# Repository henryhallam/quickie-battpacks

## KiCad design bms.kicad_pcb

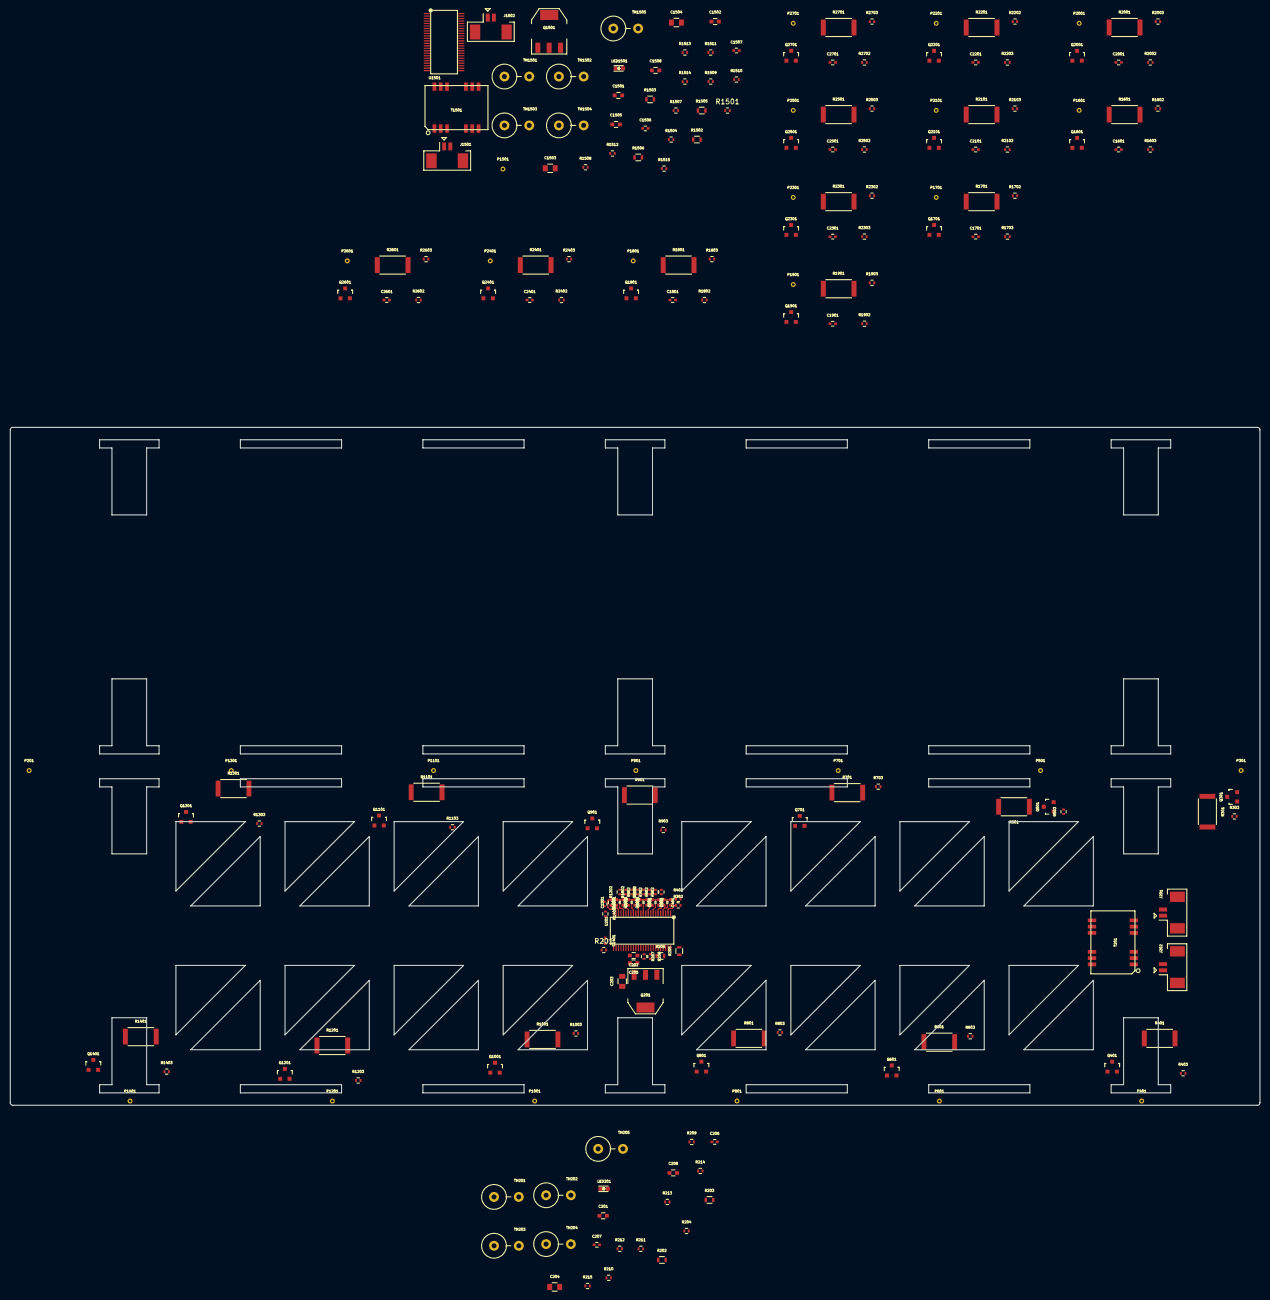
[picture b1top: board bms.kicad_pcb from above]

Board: 2 copper layers, 252.0 x 136.7 mm, 214 parts (0 on the bottom side), 174 nets.

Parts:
C201, C1501: 10nF 16V; C_0603
C202, C205, C208, C1502, C1505, C1508: 1uF 16V; C_0603
C203, C204, C1503, C1504: 0.1uF 100V; C_0805
C206, C207, C1506, C1507: 100pF; C_0402
C301, C401, C501, C601, C701, C801, C901, C1001, C1101, C1201, C1301, C1401, C1601, C1701, C1801, C1901, C2001, C2101, C2201, C2301, C2401, C2501, C2601, C2701: 10nF 16V; C_0402
J201, J202, J1501, J1502: CONN_01X02; Molex_PicoBlade_53261-0271
LED201, LED1501: Led_Small; LED_0603
P201, P301, P401, P501, P601, P701, P801, P901, P1001, P1101, P1201, P1301, P1401, P1501, P1601, P1701, P1801, P1901, P2001, P2101, P2201, P2301, P2401, P2501, P2601, P2701: CONN_01X01; Solder_Point_Round-TH_0.5mm
Q201, Q1501: NSV1C201MZ4; SOT-223
Q301, Q401, Q501, Q601, Q701, Q801, Q901, Q1001, Q1101, Q1201, Q1301, Q1401, Q1601, Q1701, Q1801, Q1901, Q2001, Q2101, Q2201, Q2301, Q2401, Q2501, Q2601, Q2701: DMP3130LQ; SOT-23
R201, R302, R402, R502, R602, R702, R802, R902, R1002, R1102, R1202, R1302, R1402, R1501, R1602, R1702, R1802, R1902, R2002, R2102, R2202, R2302, R2402, R2502, R2602, R2702: 100; R_0402
R202, R203, R1502, R1503: 100; R_0603
R204, R215, R1504, R1515: 1.2k; R_0402
R205, R206, R1505, R1506: 120; R_0603
R207, R208, R210, R211, R212, R213, R214, R1507, R1508, R1510, R1511, R1512, R1513, R1514: 10k; R_0402
R209, R1509: 2.8k; R_0402
R301, R401, R501, R601, R701, R801, R901, R1001, R1101, R1201, R1301, R1401, R1601, R1701, R1801, R1901, R2001, R2101, R2201, R2301, R2401, R2501, R2601, R2701: 10; R_2512
R303, R403, R503, R603, R703, R803, R903, R1003, R1103, R1203, R1303, R1403, R1603, R1703, R1803, R1903, R2003, R2103, R2203, R2303, R2403, R2503, R2603, R2703: 3.3k; R_0402
T201, T1501: HX0068ANL
TH201, TH202, TH203, TH204, TH205, TH1501, TH1502, TH1503, TH1504, TH1505: THERMISTOR; Resistor_Vertical_RM5mm
U201, U1501: LTC6804-1; G-SSOP-48

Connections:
/PackA/C0: C201.2, C1401.2, R201.2, U201.26
/PackA/C1: C1301.2, C1401.1, R1402.1, U201.24
/PackA/C2: C1201.2, C1301.1, R1302.1, U201.22
/PackA/C3: C1101.2, C1201.1, R1202.1, U201.20
/PackA/C4: C1001.2, C1101.1, R1102.1, U201.18
/PackA/C5: C901.2, C1001.1, R1002.1, U201.16
/PackA/C6: C801.2, C901.1, R902.1, U201.14
/PackA/C7: C701.2, C801.1, R802.1, U201.12
/PackA/C8: C601.2, C701.1, R702.1, U201.10
/PackA/C9: C501.2, C601.1, R602.1, U201.8
/PackA/C10: C401.2, C501.1, R502.1, U201.6
/PackA/C11: C301.2, C401.1, R402.1, U201.4
/PackA/C12: C301.1, R302.1, U201.2
/PackA/Cell1/Cell+: P1401.1, Q1401.2, R1301.2, R1402.2
/PackA/Cell2/Cell+: P1301.1, Q1301.2, R1201.2, R1302.2
/PackA/Cell3/Cell+: P1201.1, Q1201.2, R1101.2, R1202.2
/PackA/Cell4/Cell+: P1101.1, Q1101.2, R1001.2, R1102.2
/PackA/Cell5/Cell+: P1001.1, Q1001.2, R901.2, R1002.2
/PackA/Cell6/Cell+: P901.1, Q901.2, R801.2, R902.2
/PackA/Cell7/Cell+: P801.1, Q801.2, R701.2, R802.2
/PackA/Cell8/Cell+: P701.1, Q701.2, R601.2, R702.2
/PackA/Cell9/Cell+: P601.1, Q601.2, R501.2, R602.2
/PackA/Cell10/Cell+: P501.1, Q501.2, R401.2, R502.2
/PackA/Cell11/Cell+: P401.1, Q401.2, R301.2, R402.2
/PackA/DRIVE: Q201.1, U201.38
/PackA/Pack+: P301.1, Q301.2, R202.2, R203.2, R302.2
/PackA/S1: R1403.1, U201.25
/PackA/S2: R1303.1, U201.23
/PackA/S3: R1203.1, U201.21
/PackA/S4: R1103.1, U201.19
/PackA/S5: R1003.1, U201.17
/PackA/S6: R903.1, U201.15
/PackA/S7: R803.1, U201.13
/PackA/S8: R703.1, U201.11
/PackA/S9: R603.1, U201.9
/PackA/S10: R503.1, U201.7
/PackA/S11: R403.1, U201.5
/PackA/S12: R303.1, U201.3
/PackA/TEMP1: R210.1, TH201.1, U201.27
/PackA/TEMP2: R211.1, TH202.1, U201.28
/PackA/TEMP3: R212.1, TH203.1, U201.29
/PackA/TEMP4: R213.1, TH204.1, U201.32
/PackA/TEMP5: LED201.1, R214.1, TH205.1, U201.33
/PackA/V+: C204.1, R202.1, U201.1
/PackA/V-: C201.1, C202.2, C203.2, C204.2, C205.2, C206.2, C207.2, C208.2, P201.1, R201.1, R204.2, R1401.2, TH201.2, TH202.2, TH203.2, TH204.2, TH205.2, U201.30, U201.31
/PackA/VREF1: C202.1, U201.35
/PackA/VREF2: C205.1, R210.2, R211.2, R212.2, R213.2, R214.2, U201.34
/PackA/VREG: C208.1, Q201.3, R207.2, R208.2, R215.2, U201.37
/PackA/isoSPIA+: J202.1, T201.1
/PackA/isoSPIA-: J202.2, T201.2
/PackB/C0: C1501.2, C2701.2, R1501.2, U1501.26
/PackB/C1: C2601.2, C2701.1, R2702.1, U1501.24
/PackB/C2: C2501.2, C2601.1, R2602.1, U1501.22
/PackB/C3: C2401.2, C2501.1, R2502.1, U1501.20
/PackB/C4: C2301.2, C2401.1, R2402.1, U1501.18
/PackB/C5: C2201.2, C2301.1, R2302.1, U1501.16
/PackB/C6: C2101.2, C2201.1, R2202.1, U1501.14
/PackB/C7: C2001.2, C2101.1, R2102.1, U1501.12
/PackB/C8: C1901.2, C2001.1, R2002.1, U1501.10
/PackB/C9: C1801.2, C1901.1, R1902.1, U1501.8
/PackB/C10: C1701.2, C1801.1, R1802.1, U1501.6
/PackB/C11: C1601.2, C1701.1, R1702.1, U1501.4
/PackB/C12: C1601.1, R1602.1, U1501.2
/PackB/Cell1/Cell+: P2701.1, Q2701.2, R2601.2, R2702.2
/PackB/Cell2/Cell+: P2601.1, Q2601.2, R2501.2, R2602.2
/PackB/Cell3/Cell+: P2501.1, Q2501.2, R2401.2, R2502.2
/PackB/Cell4/Cell+: P2401.1, Q2401.2, R2301.2, R2402.2
/PackB/Cell5/Cell+: P2301.1, Q2301.2, R2201.2, R2302.2
/PackB/Cell6/Cell+: P2201.1, Q2201.2, R2101.2, R2202.2
/PackB/Cell7/Cell+: P2101.1, Q2101.2, R2001.2, R2102.2
/PackB/Cell8/Cell+: P2001.1, Q2001.2, R1901.2, R2002.2
/PackB/Cell9/Cell+: P1901.1, Q1901.2, R1801.2, R1902.2
/PackB/Cell10/Cell+: P1801.1, Q1801.2, R1701.2, R1802.2
/PackB/Cell11/Cell+: P1701.1, Q1701.2, R1601.2, R1702.2
/PackB/DRIVE: Q1501.1, U1501.38
/PackB/Pack+: P1601.1, Q1601.2, R1502.2, R1503.2, R1602.2
/PackB/S1: R2703.1, U1501.25
/PackB/S2: R2603.1, U1501.23
/PackB/S3: R2503.1, U1501.21
/PackB/S4: R2403.1, U1501.19
/PackB/S5: R2303.1, U1501.17
/PackB/S6: R2203.1, U1501.15
/PackB/S7: R2103.1, U1501.13
/PackB/S8: R2003.1, U1501.11
/PackB/S9: R1903.1, U1501.9
/PackB/S10: R1803.1, U1501.7
/PackB/S11: R1703.1, U1501.5
/PackB/S12: R1603.1, U1501.3
/PackB/TEMP1: R1510.1, TH1501.1, U1501.27
/PackB/TEMP2: R1511.1, TH1502.1, U1501.28
/PackB/TEMP3: R1512.1, TH1503.1, U1501.29
/PackB/TEMP4: R1513.1, TH1504.1, U1501.32
/PackB/TEMP5: LED1501.1, R1514.1, TH1505.1, U1501.33
/PackB/V+: C1504.1, R1502.1, U1501.1
/PackB/V-: C1501.1, C1502.2, C1503.2, C1504.2, C1505.2, C1506.2, C1507.2, C1508.2, P1501.1, R1501.1, R1504.2, R2701.2, TH1501.2, TH1502.2, TH1503.2, TH1504.2, TH1505.2, U1501.30, U1501.31
/PackB/VREF1: C1502.1, U1501.35
/PackB/VREF2: C1505.1, R1510.2, R1511.2, R1512.2, R1513.2, R1514.2, U1501.34
/PackB/VREG: C1508.1, Q1501.3, R1507.2, R1508.2, R1515.2, U1501.37
/PackB/isoSPIB+: J1501.1, T1501.5
/PackB/isoSPIB-: J1501.2, T1501.6
/isoSPI_P2P_+: J201.1, J1502.1, T201.5, T1501.1
/isoSPI_P2P_-: J201.2, J1502.2, T201.6, T1501.2
unnamed: C203.1, Q201.2, Q201.4, R203.1
unnamed: C206.1, T201.10
unnamed: C207.1, T201.9
unnamed: C1503.1, Q1501.2, Q1501.4, R1503.1
unnamed: C1506.1, T1501.10
unnamed: C1507.1, T1501.9
unnamed: LED201.2, R215.1
unnamed: LED1501.2, R1515.1
unnamed: Q301.1, R303.2
unnamed: Q301.3, R301.1
unnamed: Q401.1, R403.2
unnamed: Q401.3, R401.1
unnamed: Q501.1, R503.2
unnamed: Q501.3, R501.1
unnamed: Q601.1, R603.2
unnamed: Q601.3, R601.1
unnamed: Q701.1, R703.2
unnamed: Q701.3, R701.1
unnamed: Q801.1, R803.2
unnamed: Q801.3, R801.1
unnamed: Q901.1, R903.2
unnamed: Q901.3, R901.1
unnamed: Q1001.1, R1003.2
unnamed: Q1001.3, R1001.1
unnamed: Q1101.1, R1103.2
unnamed: Q1101.3, R1101.1
unnamed: Q1201.1, R1203.2
unnamed: Q1201.3, R1201.1
unnamed: Q1301.1, R1303.2
unnamed: Q1301.3, R1301.1
unnamed: Q1401.1, R1403.2
unnamed: Q1401.3, R1401.1
unnamed: Q1601.1, R1603.2
unnamed: Q1601.3, R1601.1
unnamed: Q1701.1, R1703.2
unnamed: Q1701.3, R1701.1
unnamed: Q1801.1, R1803.2
unnamed: Q1801.3, R1801.1
unnamed: Q1901.1, R1903.2
unnamed: Q1901.3, R1901.1
unnamed: Q2001.1, R2003.2
unnamed: Q2001.3, R2001.1
unnamed: Q2101.1, R2103.2
unnamed: Q2101.3, R2101.1
unnamed: Q2201.1, R2203.2
unnamed: Q2201.3, R2201.1
unnamed: Q2301.1, R2303.2
unnamed: Q2301.3, R2301.1
unnamed: Q2401.1, R2403.2
unnamed: Q2401.3, R2401.1
unnamed: Q2501.1, R2503.2
unnamed: Q2501.3, R2501.1
unnamed: Q2601.1, R2603.2
unnamed: Q2601.3, R2601.1
unnamed: Q2701.1, R2703.2
unnamed: Q2701.3, R2701.1
unnamed: R204.1, R209.2, U201.46
unnamed: R205.1, T201.7, U201.47
unnamed: R205.2, T201.8, U201.48
unnamed: R206.1, T201.11, U201.41
unnamed: R206.2, T201.12, U201.42
unnamed: R207.1, U201.36
unnamed: R208.1, U201.40
unnamed: R209.1, U201.45
unnamed: R1504.1, R1509.2, U1501.46
unnamed: R1505.1, T1501.7, U1501.47
unnamed: R1505.2, T1501.8, U1501.48
unnamed: R1506.1, T1501.11, U1501.41
unnamed: R1506.2, T1501.12, U1501.42
unnamed: R1507.1, U1501.36
unnamed: R1508.1, U1501.40
unnamed: R1509.1, U1501.45

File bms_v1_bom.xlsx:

Reference Designator | Quantity | Description/Value | Manufacturer Part Number (MPN)
REF**,REF**,REF**,REF**,REF**,REF**,REF** | 7 | Fiducials | DNP
C501,C301,C401,C601,C701,C801,C901,C1001,C1101,C1201,C1301,C1401,C201,C1501,C16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 | 26 | CAP CER 0.01uF 50V | GCM155R71H103KA55D
C202,C205,C208,C1502,C1505,C1508 | 6 | CAP CER 1uF 16V | GCM188R71C105KA64D
C203,C204,C1503,C1504 | 4 | CAP CER 0.1uF 250V | CGA4J3X7T2E104M125AE
J201,J202,J1501,J1502 | 4 | Conn Picoblade 2pos | 53261-0271
Q201,Q1501 | 2 | Transistor NPN | NSV1C201MZ4
Q301,Q401,Q501,Q601,Q701,Q801,Q901,Q1001,Q1101,Q1201,Q1301,Q1401,Q1601,Q1701,Q1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 | 24 | MOSFET P-CH 3A | DMP3130LQ
R202,R203,R1502,R1503 | 4 | RES 100R 1% | ERJ-3EKF1000V
R205,R206,R1505,R1506 | 4 | RES 120R 1% | ERJ-3EKF1200V
R301,R401,R501,R601,R701,R801,R901,R1001,R1101,R1201,R1301,R1401,R1601,R1701,R1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 | 24 | RES 10R 5% 3W | 352210RJT
T201,T1501 | 2 | Transformer pulse | HX0068ANL
U201,U1501 | 2 | IC MONITOR BATT STACK | LTC6804HG-1
P201,P301,P401,P501,P601,P701,P801,P901,P1001,P1101,P1201,P1301,P1401,P1501,P16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 | 26 | Solder point | DNP
C206,C207,C1506,C1507 | 4 | CAP CER 100pF 50V | CGJ2B2C0G1H101J050BA
R204,R1504 | 2 | RES 1.2K 1% | ERJ-2RKF1201X
R207,R208,R210,R211,R212,R213,R214,R1507,R1508,R1510,R1511,R1512,R1513,R1514 | 14 | RES 10K 0.1% | ERA-2AEB103X
R302,R402,R502,R602,R702,R802,R902,R1002,R1102,R1202,R1302,R1402,R201,R1501,R16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 | 26 | RES 100R 1% | ERJ-2RKF1000X
R209,R303,R403,R503,R603,R703,R803,R903,R1003,R1103,R1203,R1303,R1403,R1509,R16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 | 24 | RES 2.8K 1% | ERJ-2RKF2801X
D201,D1501 | 2 | DIODE GEN PURP SOD523 | 1N4148X
LED201,LED202,LED1501,LED1502 | 4 | LED 0402 YEL/GRN | SML-P12MTT86R
TH201,TH202,TH203,TH204,TH205,TH1501,TH1502,TH1503,TH1504,TH1505 | 10 | Thermistors | DNP

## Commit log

2017-09-25 Change to mostly 0402 passives
2017-09-25 Fix trace-across-cutout
2017-09-25 Dual-pack version, schematic complete but not all footprints / parts assigned
2017-09-25 pack A routing complete?
2017-09-25 Headnode schematic progress; chose power supply modules
2017-09-25 Add access holes for screws
2017-09-25 routuing progress
2017-09-25 Netlist exported
2017-09-25 isospi diff pairs routed
2017-09-25 place RC filter resistors
2017-09-25 Footprints assigned, some MFNs
2017-09-25 placement progress
2017-09-25 bms.pretty/Solder_Point_Round-TH_0.5mm.kicad_mod
2017-09-25 Clone layout to pack B
2017-09-25 very rough placement of cell subcircuits
2017-09-25 place and route filter caps
2017-09-25 Board outline and slots for spacer plates
2017-09-25 Headnote schematic WIP
2017-09-25 Change LED and thermistors
2017-09-25 sense paths routed
2017-09-25 Added missing series connections
2017-09-25 routing progress
2017-09-25 Approx placement complete
2017-09-25 ERC fixes
2017-09-25 BOM as sent to Tempo
2017-09-25 Place balance wire solder points for pack A
2017-09-25 Unfinished headnode
2017-09-25 pack A silkscreen
2017-09-25 discharge paths routed
